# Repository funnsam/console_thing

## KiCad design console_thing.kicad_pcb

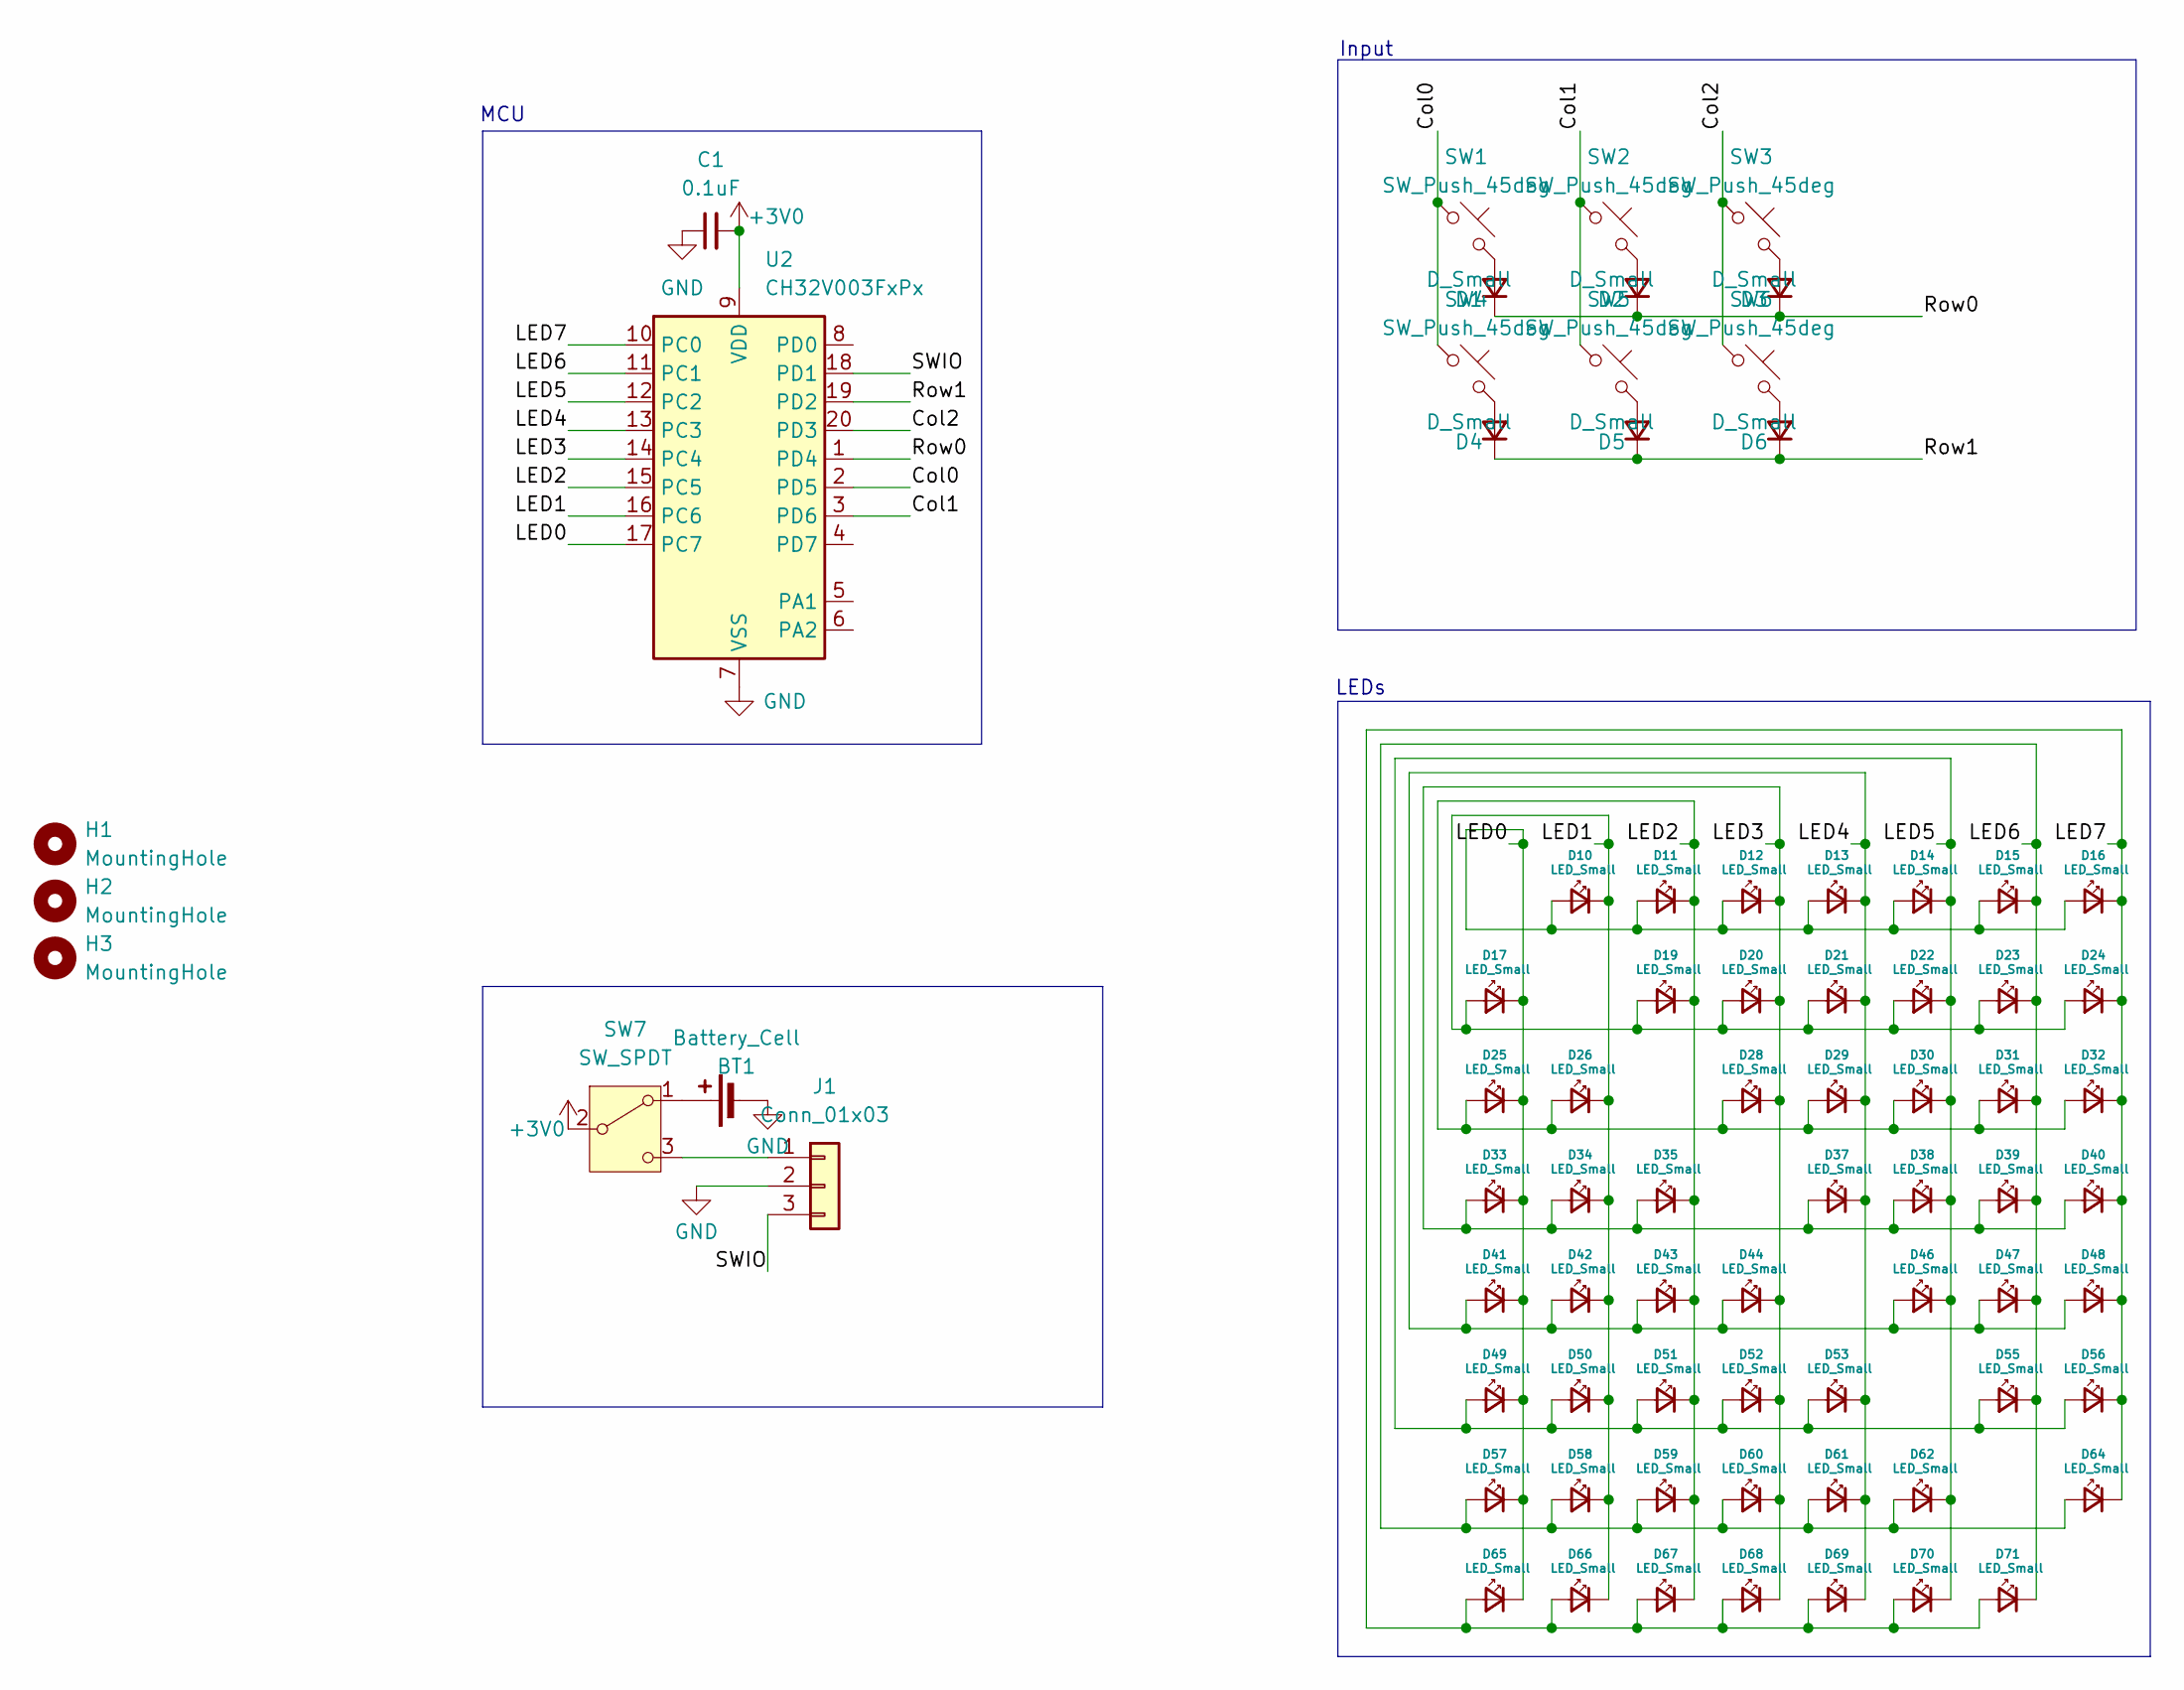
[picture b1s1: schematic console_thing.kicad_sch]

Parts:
BT1: Battery_Cell; BatteryHolder_Keystone_1058_1x2032
C1: 0.1uF; C_0805_2012Metric
D1, D2, D3, D4, D5, D6: D_Small; D_0805_2012Metric
D10, D11, D12, D13, D14, D15, D16, D17, D19, D20, D21, D22, D23, D24, D25, D26, D28, D29, D30, D31, D32, D33, D34, D35, D37, D38, D39, D40, D41, D42, D43, D44, D46, D47, D48, D49, D50, D51, D52, D53, D55, D56, D57, D58, D59, D60, D61, D62, D64, D65, D66, D67, D68, D69, D70, D71: LED_Small; LED_0603_1608Metric
H1, H2, H3: MountingHole; MountingHole_2.2mm_M2
J1: Conn_01x03; PinHeader_1x03_P2.54mm_Vertical
SW1, SW2, SW3, SW4, SW5, SW6: SW_Push_45deg; SW_Push_1P1T_NO_6x6mm_H9.5mm
SW7: SW_SPDT; SW_SPDT_CK_JS102011SAQN
U2: CH32V003FxPx; TSSOP-20_4.4x6.5mm_P0.65mm

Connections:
+3V0: C1.2, SW7.2 (B), U2.9 (VDD)
/Col0: SW1.1, SW4.1, U2.2 (PD5)
/Col1: SW2.1, SW5.1, U2.3 (PD6)
/Col2: SW3.1, SW6.1, U2.20 (PD3)
/LED0: D10.2 (A), D11.2 (A), D12.2 (A), D13.2 (A), D14.2 (A), D15.2 (A), D16.2 (A), D17.1 (K), D25.1 (K), D33.1 (K), D41.1 (K), D49.1 (K), D57.1 (K), D65.1 (K), U2.17 (PC7)
/LED1: D10.1 (K), D17.2 (A), D19.2 (A), D20.2 (A), D21.2 (A), D22.2 (A), D23.2 (A), D24.2 (A), D26.1 (K), D34.1 (K), D42.1 (K), D50.1 (K), D58.1 (K), D66.1 (K), U2.16 (PC6)
/LED2: D11.1 (K), D19.1 (K), D25.2 (A), D26.2 (A), D28.2 (A), D29.2 (A), D30.2 (A), D31.2 (A), D32.2 (A), D35.1 (K), D43.1 (K), D51.1 (K), D59.1 (K), D67.1 (K), U2.15 (PC5)
/LED3: D12.1 (K), D20.1 (K), D28.1 (K), D33.2 (A), D34.2 (A), D35.2 (A), D37.2 (A), D38.2 (A), D39.2 (A), D40.2 (A), D44.1 (K), D52.1 (K), D60.1 (K), D68.1 (K), U2.14 (PC4)
/LED4: D13.1 (K), D21.1 (K), D29.1 (K), D37.1 (K), D41.2 (A), D42.2 (A), D43.2 (A), D44.2 (A), D46.2 (A), D47.2 (A), D48.2 (A), D53.1 (K), D61.1 (K), D69.1 (K), U2.13 (PC3)
/LED5: D14.1 (K), D22.1 (K), D30.1 (K), D38.1 (K), D46.1 (K), D49.2 (A), D50.2 (A), D51.2 (A), D52.2 (A), D53.2 (A), D55.2 (A), D56.2 (A), D62.1 (K), D70.1 (K), U2.12 (PC2)
/LED6: D15.1 (K), D23.1 (K), D31.1 (K), D39.1 (K), D47.1 (K), D55.1 (K), D57.2 (A), D58.2 (A), D59.2 (A), D60.2 (A), D61.2 (A), D62.2 (A), D64.2 (A), D71.1 (K), U2.11 (PC1)
/LED7: D16.1 (K), D24.1 (K), D32.1 (K), D40.1 (K), D48.1 (K), D56.1 (K), D64.1 (K), D65.2 (A), D66.2 (A), D67.2 (A), D68.2 (A), D69.2 (A), D70.2 (A), D71.2 (A), U2.10 (PC0)
/Row0: D1.1 (K), D2.1 (K), D3.1 (K), U2.1 (PD4)
/Row1: D4.1 (K), D5.1 (K), D6.1 (K), U2.19 (PD2)
/SWIO: J1.3, U2.18 (PD1)
GND: BT1.2 (-), C1.1, J1.2, U2.7 (VSS)
unnamed: BT1.1 (+), SW7.1 (A)
unnamed: D1.2 (A), SW1.2
unnamed: D2.2 (A), SW2.2
unnamed: D3.2 (A), SW3.2
unnamed: D4.2 (A), SW4.2
unnamed: D5.2 (A), SW5.2
unnamed: D6.2 (A), SW6.2
unnamed: J1.1, SW7.3 (C)

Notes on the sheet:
Input
MCU
LEDs

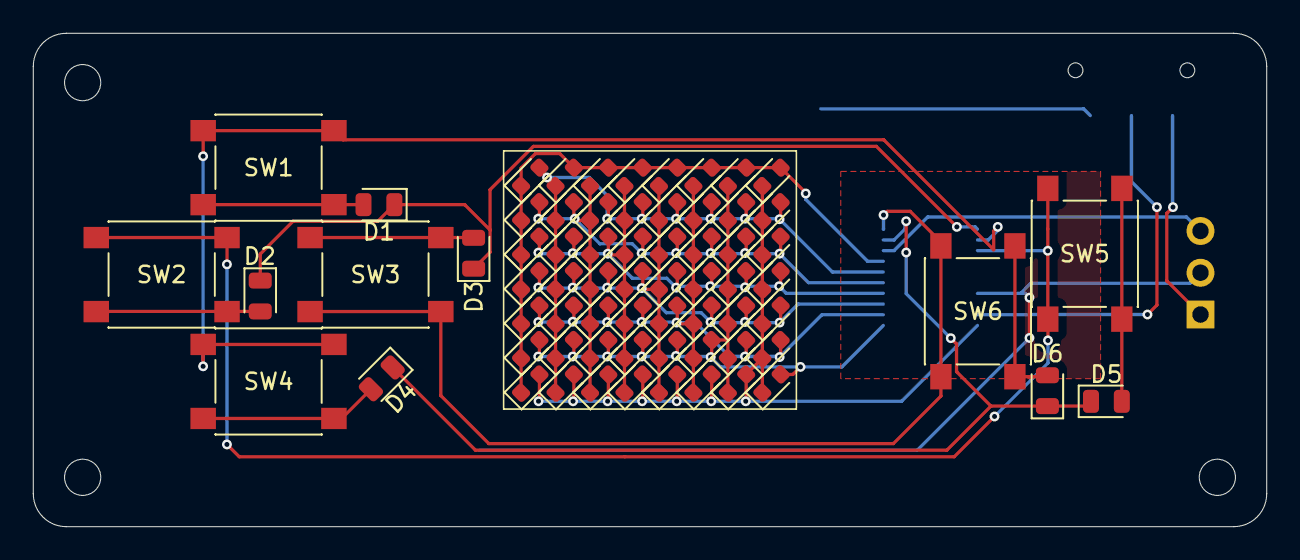
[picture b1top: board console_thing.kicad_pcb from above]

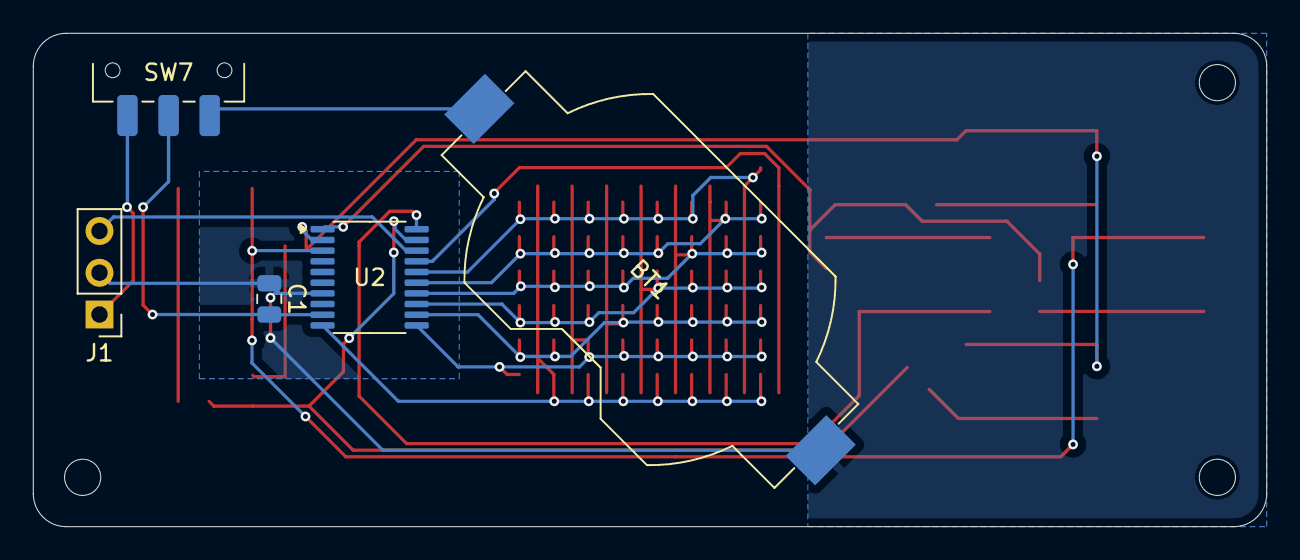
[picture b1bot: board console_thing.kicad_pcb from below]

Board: 2 copper layers, 75.0 x 30.0 mm, 76 parts (5 on the bottom side), 24 nets.

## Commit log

2024-09-22 first
2024-09-23 reroute
2024-09-24 rerouted
2024-09-24 updat
